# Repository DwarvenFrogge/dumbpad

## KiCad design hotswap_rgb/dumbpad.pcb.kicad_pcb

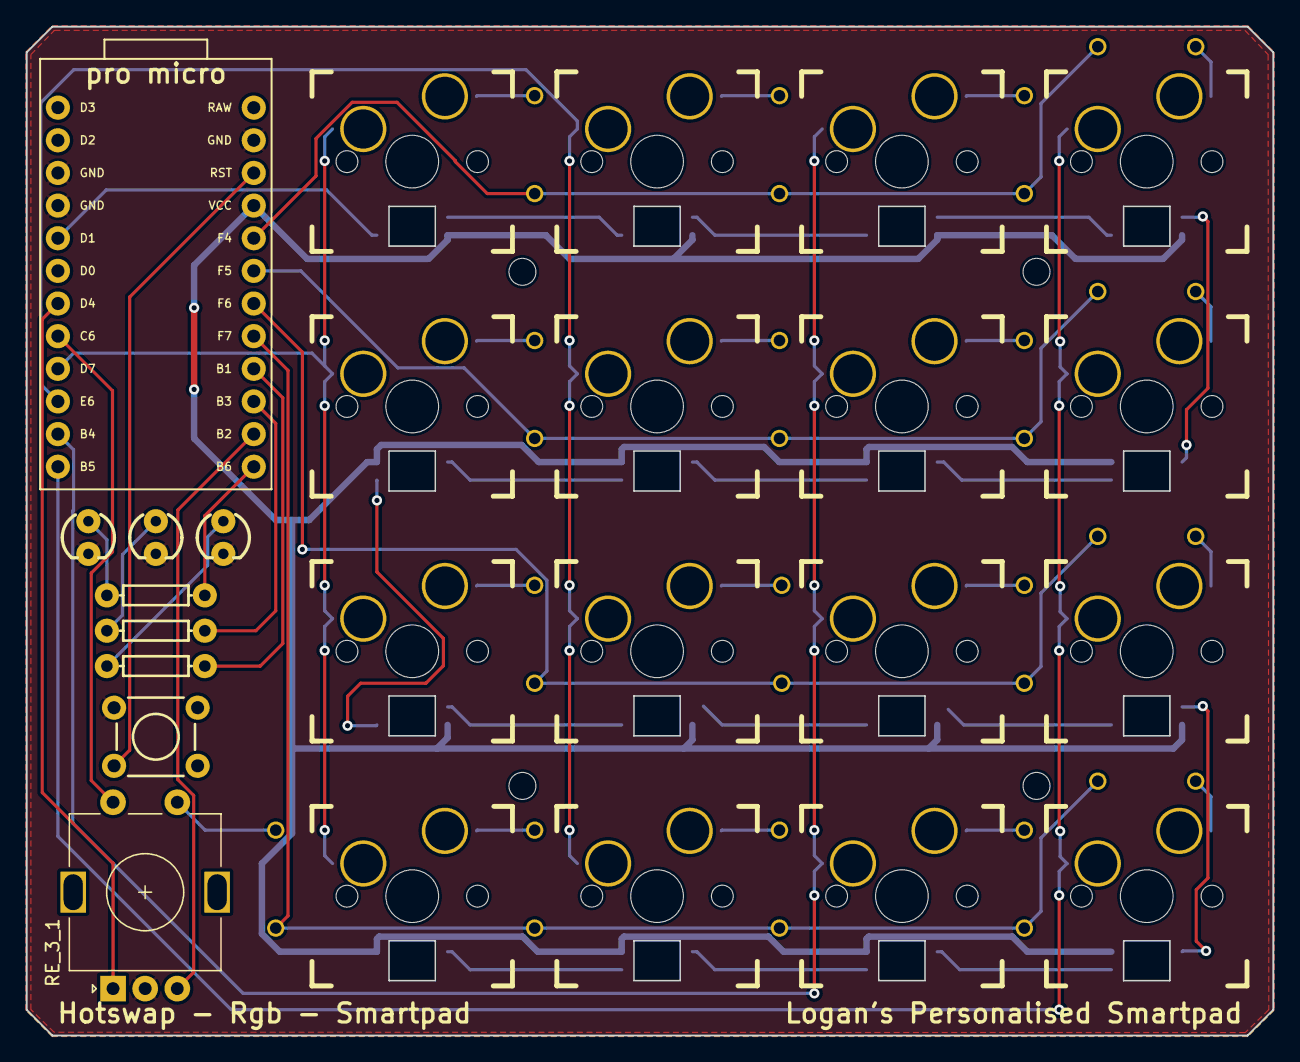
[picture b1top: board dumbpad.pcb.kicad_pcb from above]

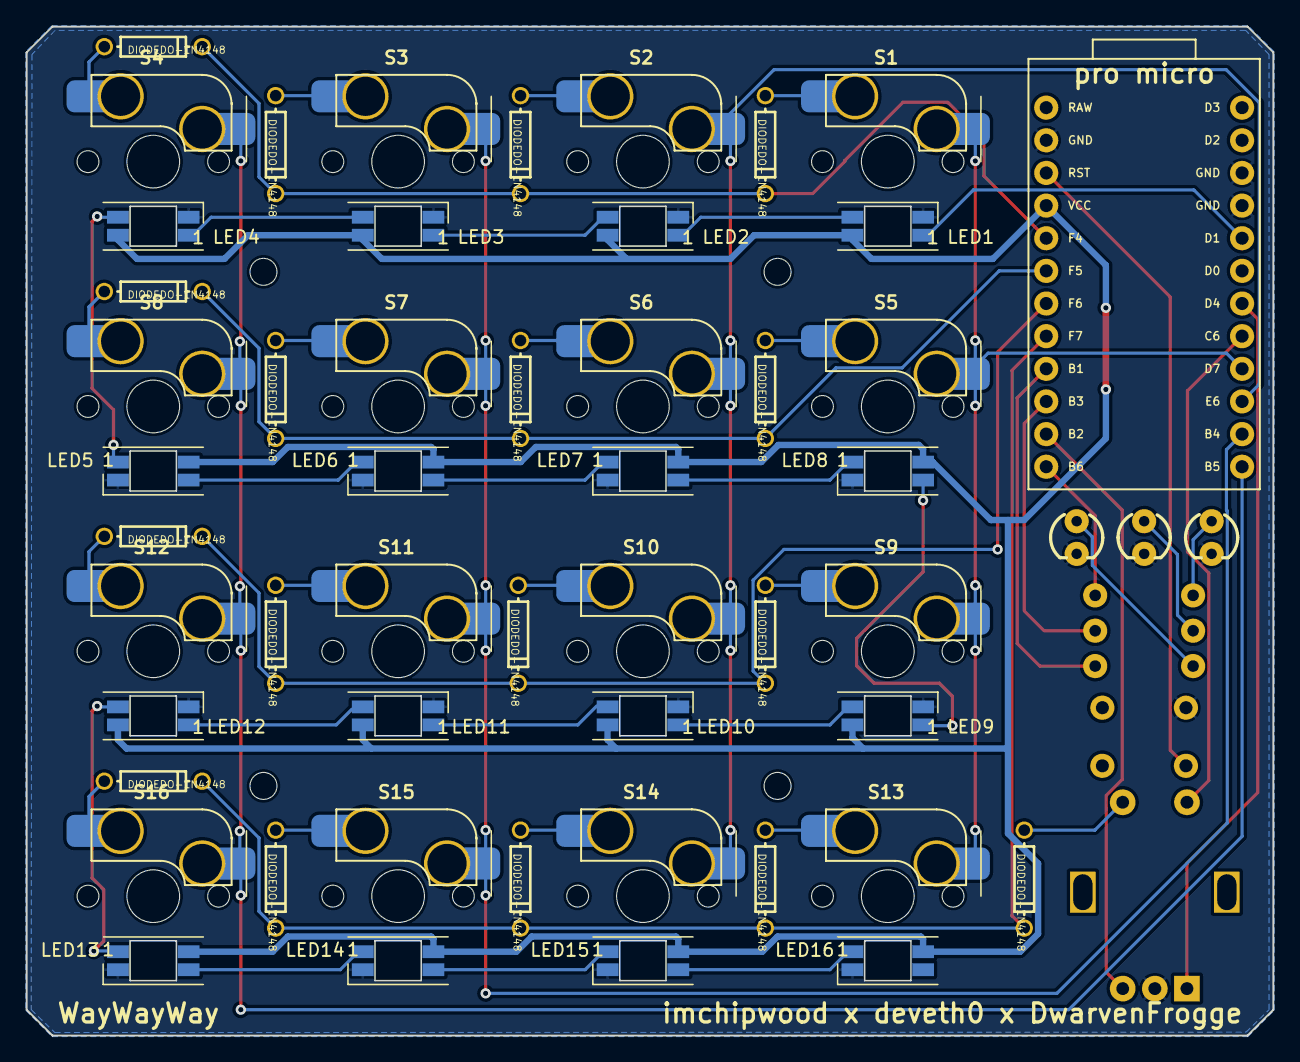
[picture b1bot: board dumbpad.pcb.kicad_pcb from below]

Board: 2 copper layers, 97.0 x 78.5 mm, 58 parts (49 on the bottom side), 53 nets.

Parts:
B1: SPARKFUN_PRO_MICRO
D1, D2, D3, D4, D5, D6, D7, D8, D9, D10, D11, D12, D13, D14, D15, D16, D20: DIODEDO-1N4148; DO-1N4148
D17, D18, D19: LED3MM; LED_3MM
LED1, LED2, LED3, LED4, LED5, LED6, LED7, LED8, LED9, LED10, LED11, LED12, LED13, LED14, LED15, LED16: SK6812MINI; YS-SK6812MINI-E
R1, R2, R3: 330; AXIAL-0.3
RE_3_1: CHERRY-MX-ENCODER; RotaryEncoder_Alps_EC11E-Switch_Vertical_H20mm
S1, S2, S3, S4, S5, S6, S7, S8, S9, S10, S11, S12, S13, S14, S15, S16: MOMENTARY-SWITCH-SPST-LED-PTH-CHERRY; Kailh-CPG151101S11_MX_Socket-1.00u
S17: MOMENTARY-SWITCH-SPST-PTH-6.0MM; TACTILE_SWITCH_PTH_6.0MM

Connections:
/COL0: B1.8 (*5), RE_3_1.S2 (2)
/COL1: B1.9 (*6), S1.S2 (2), S5.S2 (2), S9.S2 (2), S13.S2 (2)
/COL2: B1.10 (7), S2.S2 (2), S6.S2 (2), S10.S2 (2), S14.S2 (2)
/COL3: B1.11 (8), S3.S2 (2), S7.S2 (2), S11.S2 (2), S15.S2 (2)
/COL4: B1.12 (*9), S4.S2 (2), S8.S2 (2), S12.S2 (2), S16.S2 (2)
/ENCODER0_L0: B1.14 (11(MOSI)), RE_3_1.B
/ENCODER0_L1: B1.7 (4), RE_3_1.A
/KEY_LEDS: B1.5 (2), LED1.4 (DIN)
/LED0: B1.16 (13(SCK)), R3.P$2 (2)
/LED1: B1.15 (12(MISO)), R2.P$2 (2)
/LED2: B1.13 (*10), R1.P$2 (2)
/RESET: B1.22 (RESET), S17.3 (2)
/ROW0: B1.20 (A3), D1.C, D2.C, D3.C, D4.C
/ROW1: B1.19 (A2), D5.C, D6.C, D7.C, D8.C
/ROW2: B1.18 (A1), D9.C, D10.C, D11.C, D12.C
/ROW3: B1.17 (A0), D13.C, D14.C, D15.C, D16.C, D20.C
GND: B1.3 (GND@1), B1.4 (GND), B1.23 (GND@2), D17.K (C), D18.K (C), D19.K (C), LED1.3 (VSS), LED2.3 (VSS), LED3.3 (VSS), LED4.3 (VSS), LED5.3 (VSS), LED6.3 (VSS), LED7.3 (VSS), LED8.3 (VSS), LED9.3 (VSS), LED10.3 (VSS), LED11.3 (VSS), LED12.3 (VSS), LED13.3 (VSS), LED14.3 (VSS), LED15.3 (VSS), LED16.3 (VSS), RE_3_1.C, S17.1
unnamed: D1.A, S1.S1 (1)
unnamed: D2.A, S2.S1 (1)
unnamed: D3.A, S3.S1 (1)
unnamed: D4.A, S4.S1 (1)
unnamed: D5.A, S5.S1 (1)
unnamed: D6.A, S6.S1 (1)
unnamed: D7.A, S7.S1 (1)
unnamed: D8.A, S8.S1 (1)
unnamed: D9.A, S9.S1 (1)
unnamed: D10.A, S10.S1 (1)
unnamed: D11.A, S11.S1 (1)
unnamed: D12.A, S12.S1 (1)
unnamed: D13.A, S13.S1 (1)
unnamed: D14.A, S14.S1 (1)
unnamed: D15.A, S15.S1 (1)
unnamed: D16.A, S16.S1 (1)
unnamed: D17.A, R1.P$1 (1)
unnamed: D18.A, R2.P$1 (1)
unnamed: D19.A, R3.P$1 (1)
unnamed: D20.A, RE_3_1.S1 (1)
unnamed: LED1.2 (DOUT), LED2.4 (DIN)
unnamed: LED2.2 (DOUT), LED3.4 (DIN)
unnamed: LED3.2 (DOUT), LED4.4 (DIN)
unnamed: LED4.2 (DOUT), LED5.4 (DIN)
unnamed: LED5.2 (DOUT), LED6.4 (DIN)
unnamed: LED6.2 (DOUT), LED7.4 (DIN)
unnamed: LED7.2 (DOUT), LED8.4 (DIN)
unnamed: LED8.2 (DOUT), LED9.4 (DIN)
unnamed: LED10.2 (DOUT), LED11.4 (DIN)
unnamed: LED9.2 (DOUT), LED10.4 (DIN)
unnamed: LED11.2 (DOUT), LED12.4 (DIN)
unnamed: LED12.2 (DOUT), LED13.4 (DIN)
unnamed: LED13.2 (DOUT), LED14.4 (DIN)
unnamed: LED14.2 (DOUT), LED15.4 (DIN)
unnamed: LED15.2 (DOUT), LED16.4 (DIN)
VCC: B1.21 (VCC), LED1.1 (VDD), LED2.1 (VDD), LED3.1 (VDD), LED4.1 (VDD), LED5.1 (VDD), LED6.1 (VDD), LED7.1 (VDD), LED8.1 (VDD), LED9.1 (VDD), LED10.1 (VDD), LED11.1 (VDD), LED12.1 (VDD), LED13.1 (VDD), LED14.1 (VDD), LED15.1 (VDD), LED16.1 (VDD)

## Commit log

2024-10-01 new files I guess
